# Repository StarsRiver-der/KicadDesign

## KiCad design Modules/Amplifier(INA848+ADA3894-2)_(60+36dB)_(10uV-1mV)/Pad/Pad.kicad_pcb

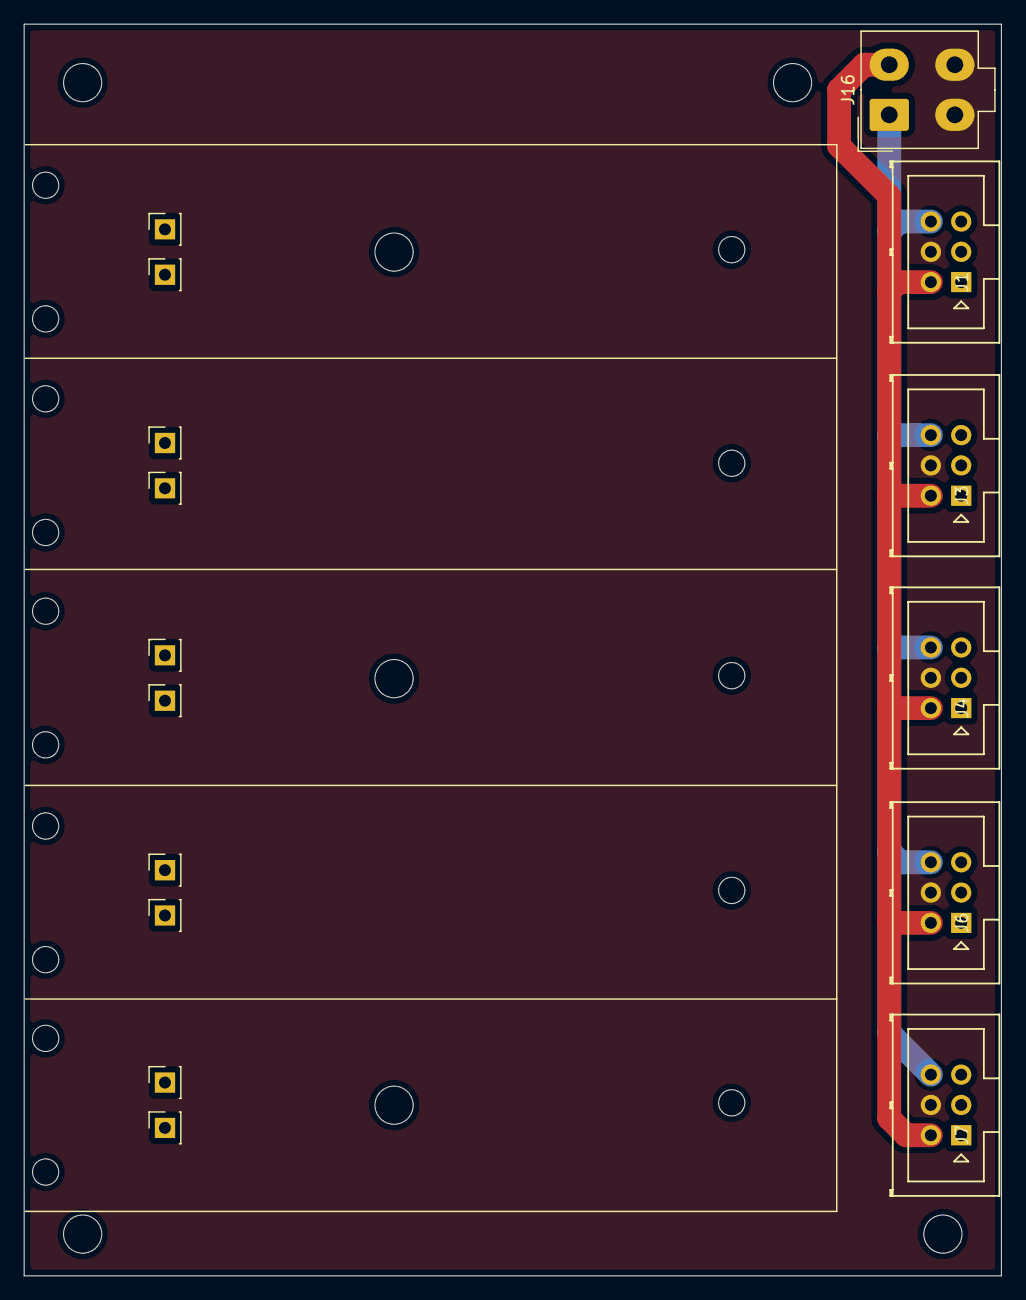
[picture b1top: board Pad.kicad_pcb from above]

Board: 4 copper layers, 81.9 x 104.9 mm, 38 parts (0 on the bottom side), 3 nets.

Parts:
H1, H2, H3, H4, H5, H6, H7, H8, H9, H10, H11, H12, H13, H14, H15: MountingHole; MountingHole_2.2mm_M2
H16, H17, H18, H19, H20, H22, H23: MountingHole; MountingHole_3.2mm_M3
J1, J3, J4, J6, J7: Conn_01x04; Multicomp_MC9A12-1034_2x03_P2.54mm_Vertical
J2, J5, J8, J9, J10, J11, J12, J13, J14, J15: Conn_01x01_Female; PinSocket_1x01_P2.54mm_Vertical
J16: Conn_01x04_Female; Molex_Mini-Fit_Jr_5566-04A_2x02_P4.20mm_Vertical

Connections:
+18V: J1.6, J3.6, J4.6, J6.6, J7.6, J16.1
-18V: J1.2, J3.2, J4.2, J6.2, J7.2, J16.2
GND: J1.4, J3.4, J4.4, J6.4, J7.4, J16.3, J16.4

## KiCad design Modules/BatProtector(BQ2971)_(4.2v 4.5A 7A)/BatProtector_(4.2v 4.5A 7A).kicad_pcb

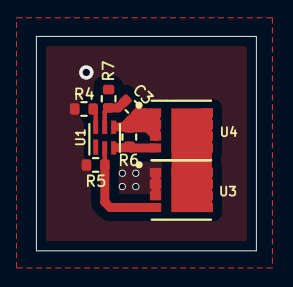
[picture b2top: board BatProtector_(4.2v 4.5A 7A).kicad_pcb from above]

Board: 2 copper layers, 12.2 x 11.9 mm, 8 parts (0 on the bottom side), 7 nets.

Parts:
C3: 0.1uF; C_0402_1005Metric
R4: 2.2k; R_0402_1005Metric
R5, R6: 5.1M; R_0402_1005Metric
R7: 330R; R_0402_1005Metric
U1: BQ2970; WSON-6_1.5x1.5mm_P0.5mm
U3, U4: CSD16406Q3

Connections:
BAT-: C3.2, R6.2, U1.4, U4.1, U4.2, U4.3
unnamed: C3.1, R7.2, U1.5
unnamed: R4.1, U1.6
unnamed: R5.1, U1.2, U3.4
unnamed: R6.1, U1.3, U4.4
unnamed: U3.5, U3.6, U3.7, U3.8, U4.5, U4.6, U4.7, U4.8
VDD: R4.2, R5.2, U3.1, U3.2, U3.3

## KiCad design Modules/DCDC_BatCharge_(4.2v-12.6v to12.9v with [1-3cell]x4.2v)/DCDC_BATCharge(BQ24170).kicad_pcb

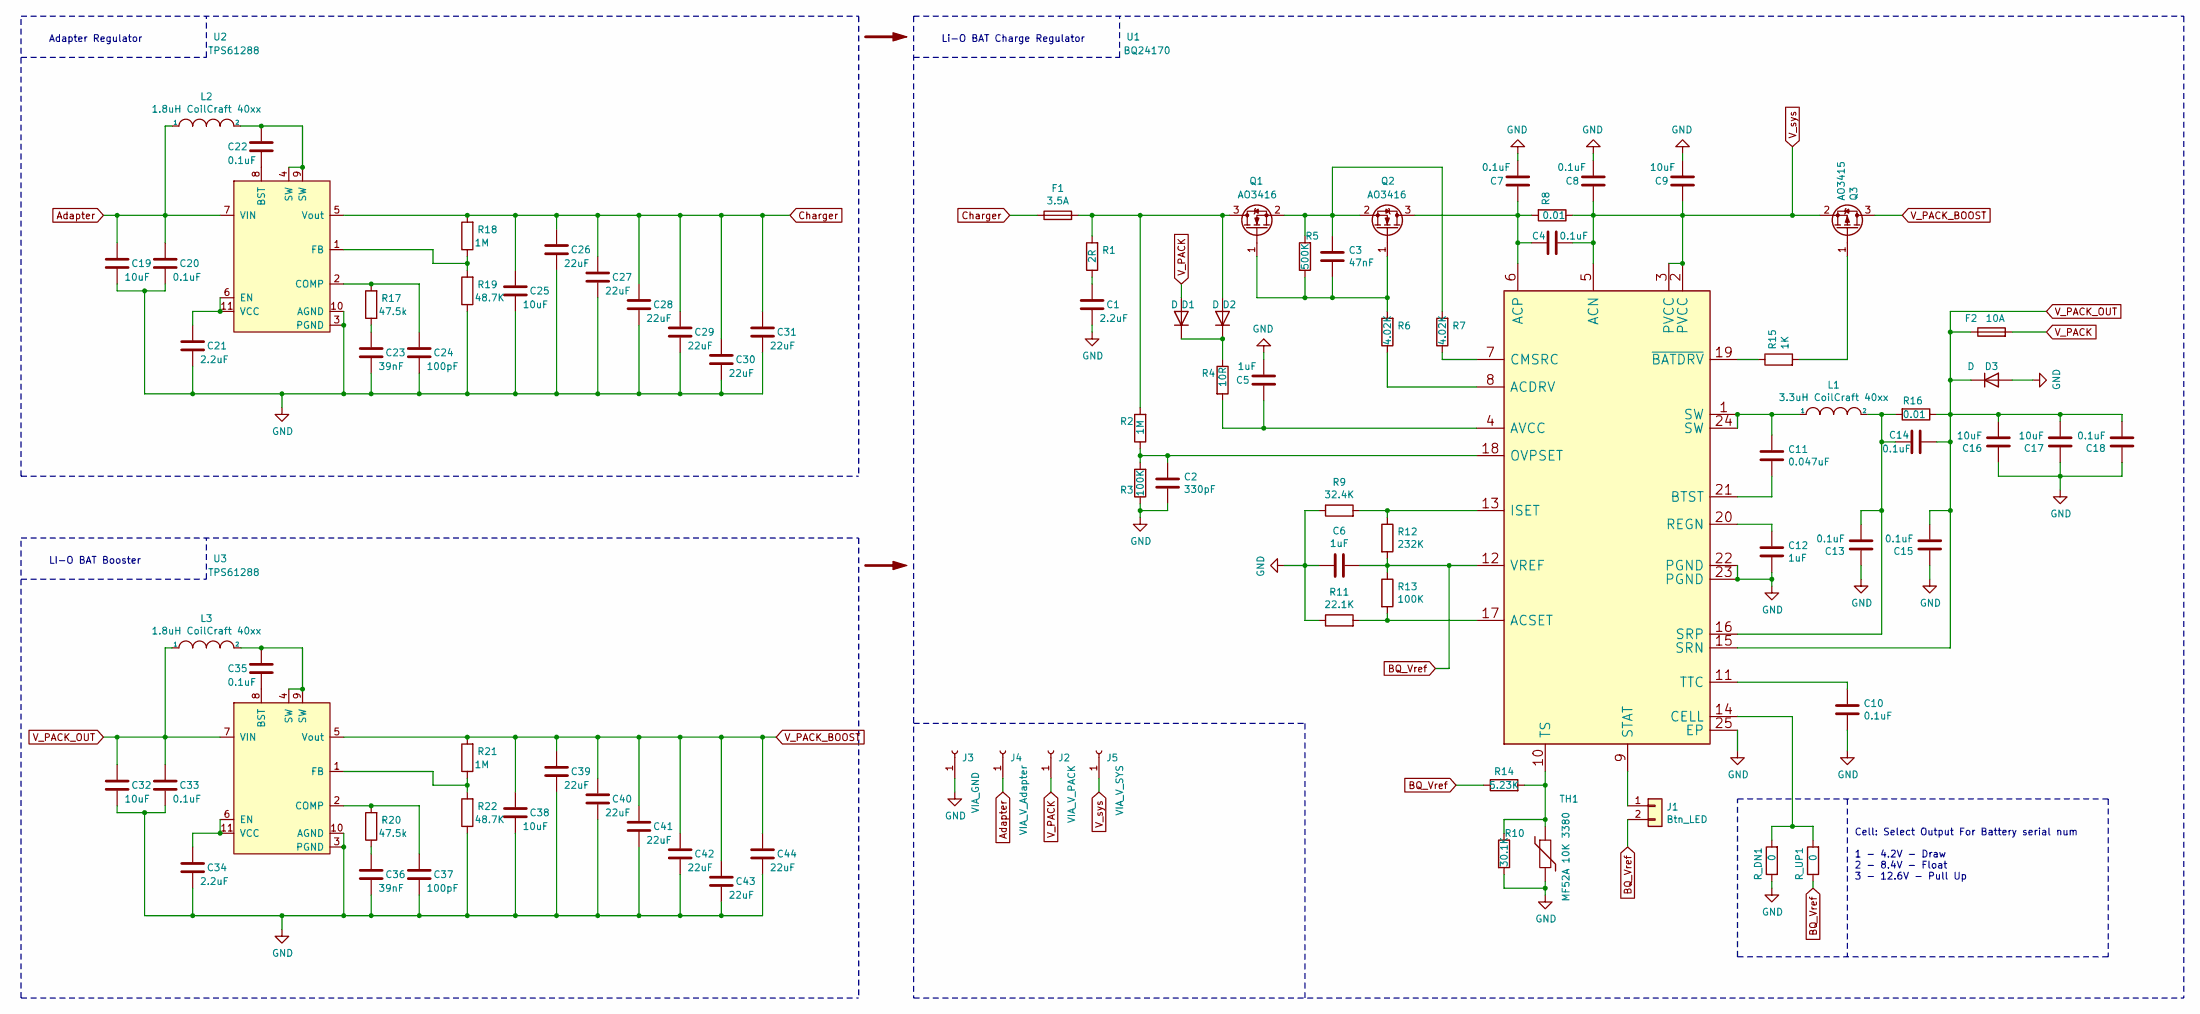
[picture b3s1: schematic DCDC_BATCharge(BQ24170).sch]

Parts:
C1, C21, C34: 2.2uF; C_0402_1005Metric
C2: 330pF; R_0402_1005Metric
C3: 47nF; C_0402_1005Metric
C4, C7, C8, C13, C14, C15, C20, C22, C33, C35: 0.1uF; C_0402_1005Metric
C5, C6, C12: 1uF; C_0603_1608Metric
C9, C16, C17: 10uF; C_0805_2012Metric
C10, C18: 0.1uF; C_0603_1608Metric
C11: 0.047uF; C_0402_1005Metric
C19, C25, C32, C38: 10uF; C_0603_1608Metric
C23, C36: 39nF; C_0402_1005Metric
C24, C37: 100pF; C_0402_1005Metric
C26, C27, C28, C29, C30, C31, C39, C40, C41, C42, C43, C44: 22uF; C_0805_2012Metric
D1, D2, D3: D; D_0603_1608Metric
F1: 3.5A; Fuse_0603_1608Metric
F2: 10A; Fuse_0603_1608Metric
J1: Btn_LED; PinHeader_1x02_P1.00mm_Vertical
J2: VIA_V_PACK; MountingHole_2.2mm_M2_Pad_Via
J3: VIA_GND; MountingHole_2.2mm_M2_Pad_Via
J4: VIA_V_Adapter; MountingHole_2.2mm_M2_Pad_Via
J5: VIA_V_SYS; MountingHole_2.2mm_M2_Pad_Via
L1: 3.3uH CoilCraft 40xx; L_Coilcraft_XxL4020
L2, L3: 1.8uH CoilCraft 40xx; L_Coilcraft_XxL4020
Q1, Q2: AO3416; SOT-23
Q3: AO3415; SOT-23
R1: 2R; R_0402_1005Metric
R2, R18, R21: 1M; R_0402_1005Metric
R3, R13: 100K; R_0402_1005Metric
R4: 10R; R_0402_1005Metric
R5: 500K; R_0402_1005Metric
R6, R7: 4.02K; R_0402_1005Metric
R8, R16: 0.01; R_0805_2012Metric
R9: 32.4K; R_0402_1005Metric
R10: 30.1K; R_0402_1005Metric
R11: 22.1K; R_0402_1005Metric
R12: 232K; R_0402_1005Metric
R14: 5.23K; R_0402_1005Metric
R15: 1K; R_0402_1005Metric
R17, R20: 47.5k; R_0402_1005Metric
R19, R22: 48.7K; R_0402_1005Metric
R_DN1: 0; R_0402_1005Metric
R_UP1: 0; R_0402_1005Metric
TH1: MF52A 10K 3380; R_Axial_DIN0204_L3.6mm_D1.6mm_P1.90mm_Vertical
U1: BQ24170; BQ24170RGYT
U2, U3: TPS61288

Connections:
Adapter: C19.2, C20.2, J4.1, L2.1, U2.7 (VIN)
BQ_Vref: C6.1, J1.2, R12.2, R13.1, R14.1, R_UP1.1, U1.12 (VREF)
Charger: C25.2, C26.2, C27.2, C28.2, C29.2, C30.2, C31.2, F1.1, R18.2, U2.5 (Vout)
GND: C1.1, C2.1, C5.1, C6.2, C7.1, C8.1, C9.1, C10.2, C12.2, C13.1, C15.1, C16.1, C17.1, C18.1, C19.1, C20.1, C21.1, C23.1, C24.1, C25.1, C26.1, C27.1, C28.1, C29.1, C30.1, C31.1, C32.1, C33.1, C34.1, C36.1, C37.1, C38.1, C39.1, C40.1, C41.1, C42.1, C43.1, C44.1, D3.2 (A), J3.1, R3.1, R9.1, R10.2, R11.1, R19.1, R22.1, R_DN1.1, TH1.2, U1.22 (PGND), U1.23 (PGND), U1.25 (EP), U2.3 (PGND), U2.10 (AGND), U3.3 (PGND), U3.10 (AGND)
unnamed: C1.2, R1.1
unnamed: C2.2, R2.1, R3.2, U1.18 (OVPSET)
unnamed: C3.1, Q1.1 (G), Q2.1 (G), R5.1, R6.2
unnamed: C3.2, Q1.2 (S), Q2.2 (S), R5.2, R7.2
unnamed: C4.1, C7.2, Q2.3 (D), R8.2, U1.6 (ACP)
unnamed: C5.2, R4.2, U1.4 (AVCC)
unnamed: C10.1, U1.11 (TTC)
unnamed: C11.1, L1.1, U1.1 (SW), U1.24 (SW)
unnamed: C11.2, U1.21 (BTST)
unnamed: C12.1, U1.20 (REGN)
unnamed: C13.2, C14.2, L1.2, R16.2, U1.16 (SRP)
unnamed: C21.2, U2.6 (EN), U2.11 (VCC)
unnamed: C22.1, U2.8 (BST)
unnamed: C22.2, L2.2, U2.4 (SW), U2.9 (SW)
unnamed: C23.2, R17.1
unnamed: C24.2, R17.2, U2.2 (COMP)
unnamed: C34.2, U3.6 (EN), U3.11 (VCC)
unnamed: C35.1, U3.8 (BST)
unnamed: C35.2, L3.2, U3.4 (SW), U3.9 (SW)
unnamed: C36.2, R20.1
unnamed: C37.2, R20.2, U3.2 (COMP)
unnamed: D1.1 (K), D2.1 (K), R4.1
unnamed: D2.2 (A), F1.2, Q1.3 (D), R1.2, R2.2
unnamed: J1.1, U1.9 (STAT)
unnamed: Q3.1 (G), R15.2
unnamed: R6.1, U1.8 (ACDRV)
unnamed: R7.1, U1.7 (CMSRC)
unnamed: R10.1, R14.2, TH1.1, U1.10 (TS)
unnamed: R11.2, R13.2, U1.17 (ACSET)
unnamed: R9.2, R12.1, U1.13 (ISET)
unnamed: R15.1, U1.19 (~BATDRV)
unnamed: R18.1, R19.2, U2.1 (FB)
unnamed: R21.1, R22.2, U3.1 (FB)
unnamed: R_DN1.2, R_UP1.2, U1.14 (CELL)
V_PACK: D1.2 (A), F2.2, J2.1
V_PACK_BOOST: C38.2, C39.2, C40.2, C41.2, C42.2, C43.2, C44.2, Q3.3 (D), R21.2, U3.5 (Vout)
V_PACK_OUT: C14.1, C15.2, C16.2, C17.2, C18.2, C32.2, C33.2, D3.1 (K), F2.1, L3.1, R16.1, U1.15 (SRN), U3.7 (VIN)
V_sys: C4.2, C8.2, C9.2, J5.1, Q3.2 (S), R8.1, U1.2 (PVCC), U1.3 (PVCC), U1.5 (ACN)

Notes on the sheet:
Li-O BAT Charge Regulator
Adapter Regulator
LI-O BAT Booster
Cell: Select Output For Battery serial num 1 - 4.2V - Draw 2 - 8.4V - Float 3 - 12.6V - Pull Up

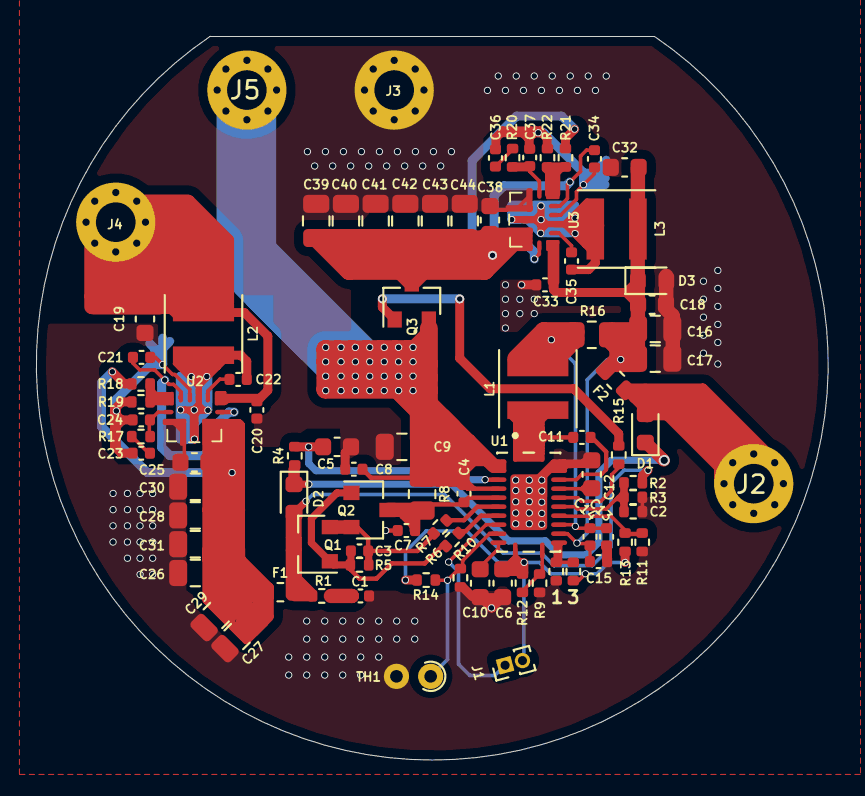
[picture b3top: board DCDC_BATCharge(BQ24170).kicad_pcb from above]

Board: 2 copper layers, 44.0 x 40.2 mm, 88 parts (0 on the bottom side), 42 nets.

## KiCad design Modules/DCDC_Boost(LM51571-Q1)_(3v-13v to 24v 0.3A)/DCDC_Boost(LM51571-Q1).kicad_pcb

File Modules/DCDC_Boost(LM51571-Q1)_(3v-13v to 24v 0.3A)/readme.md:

# 3V-13V 1-3串锂电池输入的 DCDC 升压电路
* 工作温度：0-85℃
* 最高0.8A 20W输出

# 原理
见说明手册

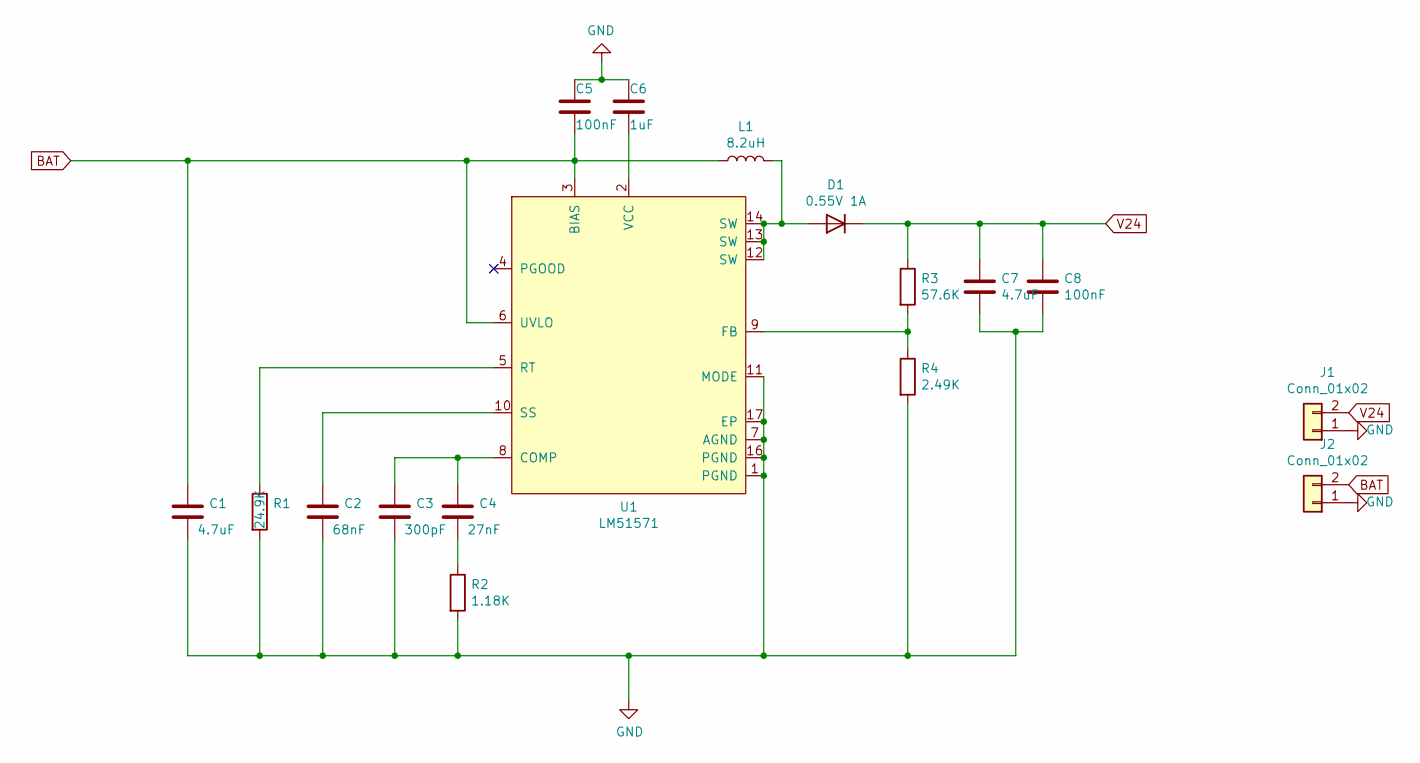
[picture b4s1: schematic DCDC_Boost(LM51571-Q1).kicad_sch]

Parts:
C1, C7: 4.7uF; C_0603_1608Metric
C2: 68nF; C_0402_1005Metric
C3: 300pF; C_0402_1005Metric
C4: 27nF; C_0402_1005Metric
C5, C8: 100nF; C_0402_1005Metric
C6: 1uF; C_0603_1608Metric
D1: 0.55V 1A; D_0603_1608Metric
J1, J2: Conn_01x02; PinHeader_1x02_P2.54mm_Vertical
L1: 8.2uH; L_Coilcraft_XxL4020
R1: 24.9K; R_0402_1005Metric
R2: 1.18K; R_0402_1005Metric
R3: 57.6K; R_0402_1005Metric
R4: 2.49K; R_0402_1005Metric
U1: LM51571; WQFN-16-1EP_3x3mm_P0.5mm_EP1.6x1.6mm_ThermalVias

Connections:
BAT: C1.1, C5.2, J2.2, L1.1, U1.3 (BIAS), U1.6 (UVLO)
GND: C1.2, C2.2, C3.2, C5.1, C6.1, C7.2, C8.2, J1.1, J2.1, R1.2, R2.2, R4.2, U1.1 (PGND), U1.7 (AGND), U1.11 (MODE), U1.16 (PGND), U1.17 (EP)
unnamed: C2.1, U1.10 (SS)
unnamed: C3.1, C4.1, U1.8 (COMP)
unnamed: C4.2, R2.1
unnamed: C6.2, U1.2 (VCC)
unnamed: D1.2 (A), L1.2, U1.12 (SW), U1.13 (SW), U1.14 (SW)
unnamed: R1.1, U1.5 (RT)
unnamed: R3.2, R4.1, U1.9 (FB)
V24: C7.1, C8.1, D1.1 (K), J1.2, R3.1

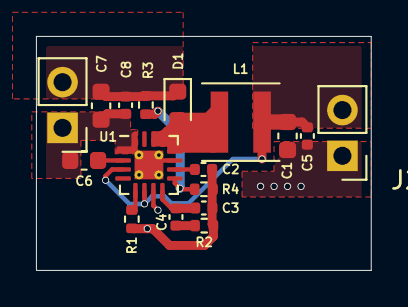
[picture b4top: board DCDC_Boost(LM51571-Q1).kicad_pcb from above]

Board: 2 copper layers, 18.6 x 13.0 mm, 17 parts (0 on the bottom side), 10 nets.

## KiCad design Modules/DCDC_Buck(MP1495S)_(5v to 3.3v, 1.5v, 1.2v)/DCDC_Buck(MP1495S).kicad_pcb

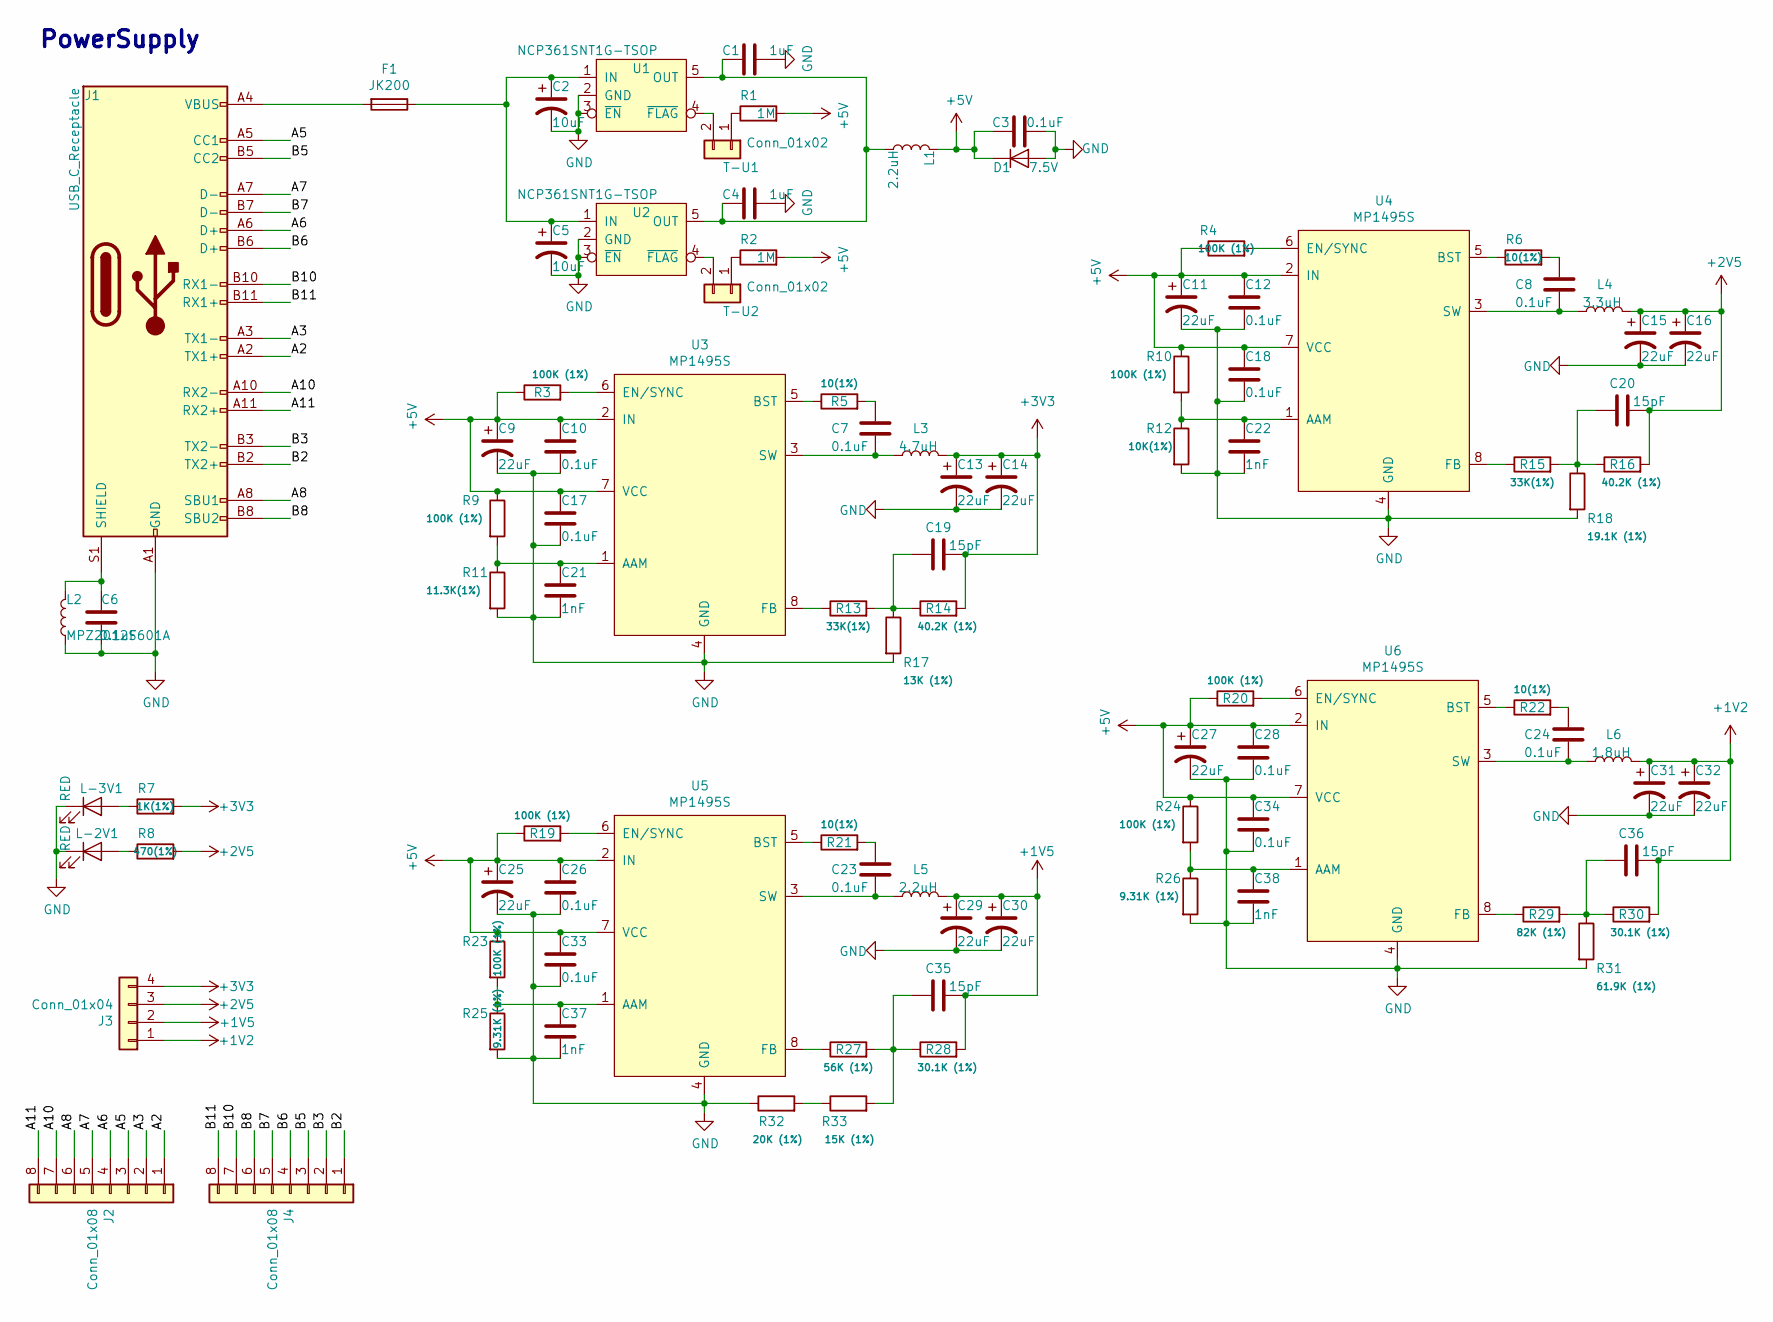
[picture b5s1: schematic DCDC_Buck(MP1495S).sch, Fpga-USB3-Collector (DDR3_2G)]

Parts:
C1, C4: 1uF; C_0603_1608Metric_Pad1.05x0.95mm_HandSolder
C2, C5: 10uF; C_0805_2012Metric_Pad1.15x1.40mm_HandSolder
C3, C6, C7, C8, C10, C12, C17, C18, C23, C24, C26, C28, C33, C34: 0.1uF; C_0603_1608Metric_Pad1.05x0.95mm_HandSolder
C9, C11, C13, C14, C15, C16, C25, C27, C29, C30, C31, C32: 22uF; C_0805_2012Metric_Pad1.15x1.40mm_HandSolder
C19, C20, C35, C36: 15pF; C_0603_1608Metric_Pad1.05x0.95mm_HandSolder
C21, C22, C37, C38: 1nF; C_0603_1608Metric_Pad1.05x0.95mm_HandSolder
D1: 7.5V; D_1206_3216Metric
F1: JK200; Fuse_2816_7142Metric_Pad3.20x4.45mm_HandSolder
J1: USB_C_Receptacle; USB_C_24pin_FtBp
J2, J4: Conn_01x08; PinHeader_1x08_P2.00mm_Vertical
J3: Conn_01x04; PinSocket_1x04_P2.54mm_Vertical
L1, L5: 2.2uH; L_Taiyo-Yuden_NR-60xx
L2: MPZ2012S601A; L_0805_2012Metric_Pad1.15x1.40mm_HandSolder
L3: 4.7uH; L_Taiyo-Yuden_NR-60xx
L4: 3.3uH; L_Taiyo-Yuden_NR-60xx
L6: 1.8uH; L_Taiyo-Yuden_NR-60xx
L-2V1, L-3V1: RED; LED_0603_1608Metric_Pad1.05x0.95mm_HandSolder
R1, R2: 1M; R_0603_1608Metric_Pad1.05x0.95mm_HandSolder
R3, R4, R9, R10, R19, R20, R23, R24: 100K (1%); R_0603_1608Metric_Pad1.05x0.95mm_HandSolder
R5, R6, R21, R22: 10(1%); R_0603_1608Metric_Pad1.05x0.95mm_HandSolder
R7: 1K(1%); R_0603_1608Metric_Pad1.05x0.95mm_HandSolder
R8: 470(1%); R_0603_1608Metric_Pad1.05x0.95mm_HandSolder
R11: 11.3K(1%); R_0603_1608Metric_Pad1.05x0.95mm_HandSolder
R12: 10K(1%); R_0603_1608Metric_Pad1.05x0.95mm_HandSolder
R13, R15: 33K(1%); R_0603_1608Metric_Pad1.05x0.95mm_HandSolder
R14, R16: 40.2K (1%); R_0603_1608Metric_Pad1.05x0.95mm_HandSolder
R17: 13K (1%); R_0603_1608Metric_Pad1.05x0.95mm_HandSolder
R18: 19.1K (1%); R_0603_1608Metric_Pad1.05x0.95mm_HandSolder
R25, R26: 9.31K (1%); R_0603_1608Metric_Pad1.05x0.95mm_HandSolder
R27: 56K (1%); R_0603_1608Metric_Pad1.05x0.95mm_HandSolder
R28, R30: 30.1K (1%); R_0603_1608Metric_Pad1.05x0.95mm_HandSolder
R29: 82K (1%); R_0603_1608Metric_Pad1.05x0.95mm_HandSolder
R31: 61.9K (1%); R_0603_1608Metric_Pad1.05x0.95mm_HandSolder
R32: 20K (1%); R_0603_1608Metric_Pad1.05x0.95mm_HandSolder
R33: 15K (1%); R_0603_1608Metric_Pad1.05x0.95mm_HandSolder
T-U1, T-U2: Conn_01x02; Pad_1x02_P2.54mm
U1, U2: NCP361SNT1G-TSOP; TSOP-5_1.65x3.05mm_P0.95mm
U3, U4, U5, U6: MP1495S; SOT65P280X100-8N

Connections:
+1V2: C31.1, C32.1, C36.2, J3.1, L6.2, R30.2
+1V5: C29.1, C30.1, C35.2, J3.2, L5.2, R28.2
+2V5: C15.1, C16.1, C20.2, J3.3, L4.2, R8.2, R16.2
+3V3: C13.1, C14.1, C19.2, J3.4, L3.2, R7.2, R14.2
+5V: C3.1, C9.1, C10.1, C11.1, C12.1, C17.1, C18.1, C25.1, C26.1, C27.1, C28.1, C33.1, C34.1, D1.1 (K), L1.1, R1.2, R2.2, R3.1, R4.1, R9.1, R10.1, R19.1, R20.1, R23.1, R24.1, U3.2 (IN), U3.7 (VCC), U4.2 (IN), U4.7 (VCC), U5.2 (IN), U5.7 (VCC), U6.2 (IN), U6.7 (VCC)
/A2: J1.A2 (TX1+), J2.1
/A3: J1.A3 (TX1-), J2.2
/A5: J1.A5 (CC1), J2.3
/A6: J1.A6 (D+), J2.4
/A7: J1.A7 (D-), J2.5
/A8: J1.A8 (SBU1), J2.6
/A10: J1.A10 (RX2-), J2.7
/A11: J1.A11 (RX2+), J2.8
/B2: J1.B2 (TX2+), J4.1
/B3: J1.B3 (TX2-), J4.2
/B5: J1.B5 (CC2), J4.3
/B6: J1.B6 (D+), J4.4
/B7: J1.B7 (D-), J4.5
/B8: J1.B8 (SBU2), J4.6
/B10: J1.B10 (RX1-), J4.7
/B11: J1.B11 (RX1+), J4.8
GND: C1.2, C2.2, C3.2, C4.2, C5.2, C6.2, C9.2, C10.2, C11.2, C12.2, C13.2, C14.2, C15.2, C16.2, C17.2, C18.2, C21.2, C22.2, C25.2, C26.2, C27.2, C28.2, C29.2, C30.2, C31.2, C32.2, C33.2, C34.2, C37.2, C38.2, D1.2 (A), J1.A1 (GND), J1.A12 (GND), J1.B1 (GND), J1.B12 (GND), L2.2, L-2V1.1 (K), L-3V1.1 (K), R11.2, R12.2, R17.2, R18.2, R25.2, R26.2, R31.2, R32.1, U1.2 (GND), U1.3 (~EN), U2.2 (GND), U2.3 (~EN), U3.4 (GND), U4.4 (GND), U5.4 (GND), U6.4 (GND)
unnamed: C1.1, C4.1, L1.2, U1.5 (OUT), U2.5 (OUT)
unnamed: C2.1, C5.1, F1.1, U1.1 (IN), U2.1 (IN)
unnamed: C6.1, J1.S1 (SHIELD), L2.1
unnamed: C7.1, R5.2
unnamed: C7.2, L3.1, U3.3 (SW)
unnamed: C8.1, R6.2
unnamed: C8.2, L4.1, U4.3 (SW)
unnamed: C19.1, R13.2, R14.1, R17.1
unnamed: C20.1, R15.2, R16.1, R18.1
unnamed: C21.1, R9.2, R11.1, U3.1 (AAM)
unnamed: C22.1, R10.2, R12.1, U4.1 (AAM)
unnamed: C23.1, R21.2
unnamed: C23.2, L5.1, U5.3 (SW)
unnamed: C24.1, R22.2
unnamed: C24.2, L6.1, U6.3 (SW)
unnamed: C35.1, R27.2, R28.1, R33.2
unnamed: C36.1, R29.2, R30.1, R31.1
unnamed: C37.1, R23.2, R25.1, U5.1 (AAM)
unnamed: C38.1, R24.2, R26.1, U6.1 (AAM)
unnamed: F1.2, J1.A4 (VBUS), J1.A9 (VBUS), J1.B4 (VBUS), J1.B9 (VBUS)
unnamed: L-2V1.2 (A), R8.1
unnamed: L-3V1.2 (A), R7.1
unnamed: R1.1, T-U1.1
unnamed: R2.1, T-U2.1
unnamed: R3.2, U3.6 (EN/SYNC)
unnamed: R4.2, U4.6 (EN/SYNC)
unnamed: R5.1, U3.5 (BST)
unnamed: R6.1, U4.5 (BST)
unnamed: R13.1, U3.8 (FB)
unnamed: R15.1, U4.8 (FB)
unnamed: R19.2, U5.6 (EN/SYNC)
unnamed: R20.2, U6.6 (EN/SYNC)
unnamed: R21.1, U5.5 (BST)
unnamed: R22.1, U6.5 (BST)
unnamed: R27.1, U5.8 (FB)
unnamed: R29.1, U6.8 (FB)
unnamed: R32.2, R33.1
unnamed: T-U1.2, U1.4 (~FLAG)
unnamed: T-U2.2, U2.4 (~FLAG)

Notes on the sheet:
PowerSupply

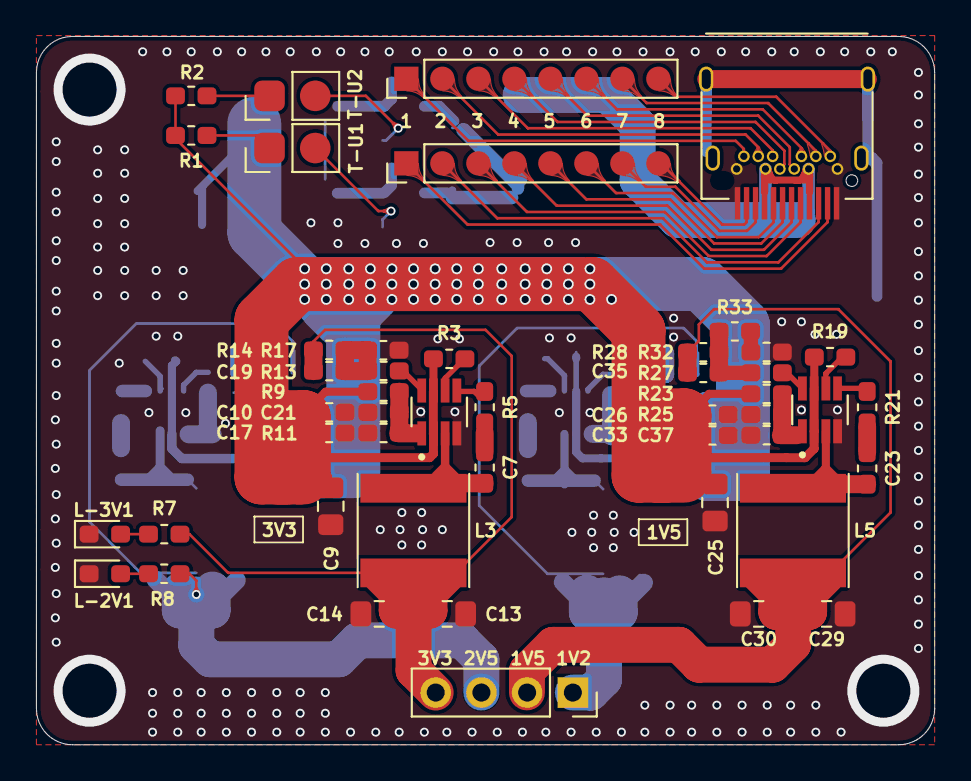
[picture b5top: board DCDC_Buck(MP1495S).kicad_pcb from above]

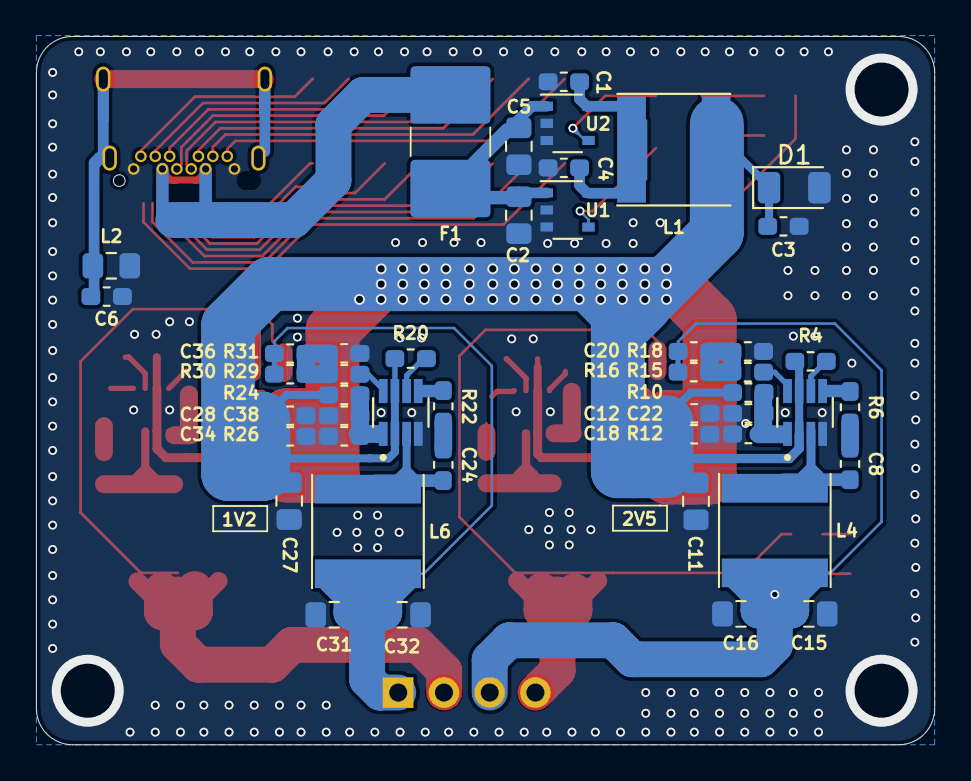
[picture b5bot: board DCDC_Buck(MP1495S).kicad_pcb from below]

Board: 2 copper layers, 49.9 x 39.4 mm, 93 parts (46 on the bottom side), 61 nets.

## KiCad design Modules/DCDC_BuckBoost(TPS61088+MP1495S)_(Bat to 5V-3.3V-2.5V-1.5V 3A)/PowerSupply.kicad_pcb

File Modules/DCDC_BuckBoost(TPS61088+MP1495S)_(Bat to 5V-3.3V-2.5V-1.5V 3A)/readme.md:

# 2.8V-4.2V 锂电池输入的 DCDC 单极性多轨电源
* 工作温度：0-85℃
* 5V、3.3V、2.5V、1.5V多轨输出
* 最高20W输出

# 原理
见说明手册

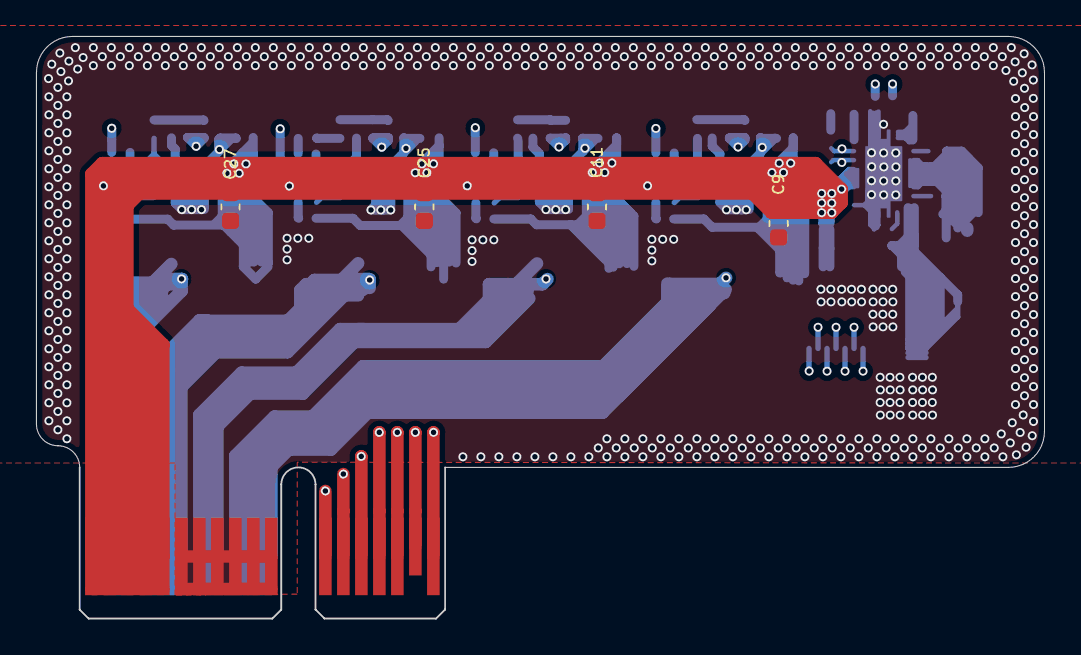
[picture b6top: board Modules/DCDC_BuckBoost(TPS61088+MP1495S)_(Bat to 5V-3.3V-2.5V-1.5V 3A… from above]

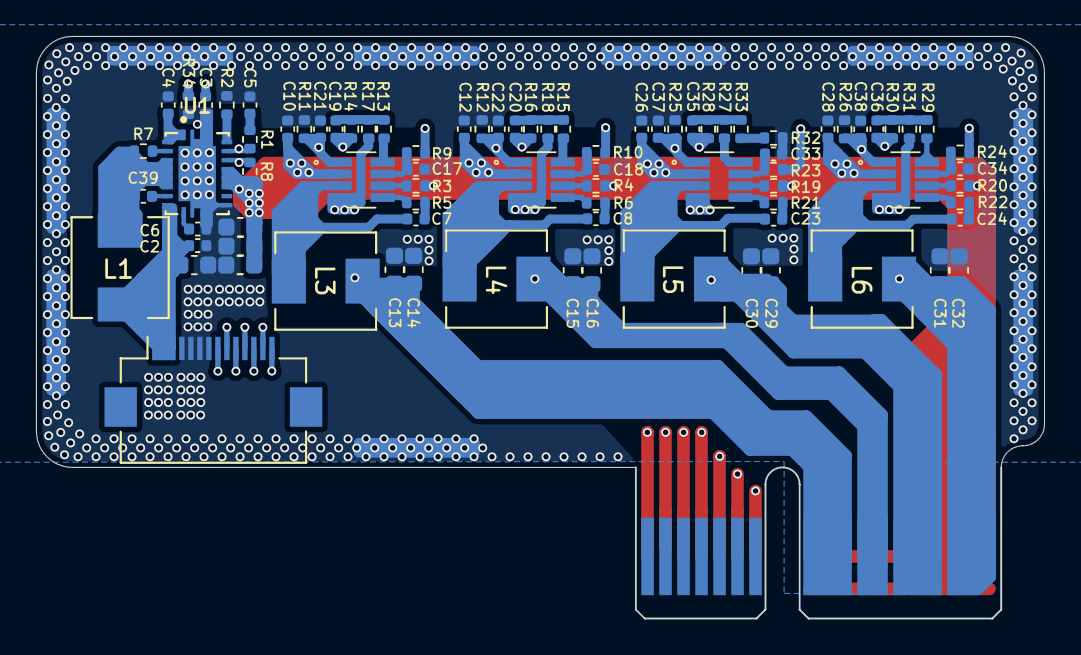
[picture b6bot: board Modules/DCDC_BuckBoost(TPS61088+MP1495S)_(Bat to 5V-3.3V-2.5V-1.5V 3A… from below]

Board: 4 copper layers, 56.0 x 32.3 mm, 97 parts (92 on the bottom side), 56 nets.

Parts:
1V2, 1V5, 2V5, 3V3: MP1495S; SOT65P280X100-8N
C1, C9, C11, C25, C27: 10uF; C_0603_1608Metric
C2, C7, C8, C10, C12, C17, C18, C23, C24, C26, C28, C33, C34, C39: 0.1uF; C_0402_1005Metric
C3: 47pF; C_0402_1005Metric
C4: 1uF; C_0402_1005Metric
C5, C21, C22, C37, C38: 1nF; C_0402_1005Metric
C6: 8.2nF; C_0402_1005Metric
C13, C14, C15, C16, C29, C30, C31, C32, C40, C41, C42: 22uF; C_0603_1608Metric
C19, C20, C35, C36: 15pF; C_0402_1005Metric
J1: Conn_01x14; Hirose_FH12-14S-0.5SH_1x14-1MP_P0.50mm_Horizontal
J2, J3, J4, J5, J6, J7, J8, J9, J10: Conn_01x01; pad-6-1.5
L1: 1uH; L_Sunlord_MWSA0518_5.4x5.2mm
L3: 4.7uH; L_Sunlord_MWSA0518_5.4x5.2mm
L4: 3.3uH; L_Sunlord_MWSA0518_5.4x5.2mm
L5: 2.2uH; L_Sunlord_MWSA0518_5.4x5.2mm
L6: 1.8uH; L_Sunlord_MWSA0518_5.4x5.2mm
PCI1: Conn_02x18_Row_Letter_First; BUS_PCIexpress_x1
R1: 23.7K; R_0402_1005Metric
R2: 113K; R_0402_1005Metric
R3, R4, R9, R10, R19, R20, R23, R24: 100K (1%); R_0402_1005Metric
R5, R6, R21, R22: 10(1%); R_0402_1005Metric
R7: 267K; R_0402_1005Metric
R8: 220K; R_0402_1005Metric
R11: 11.3K(1%); R_0402_1005Metric
R12: 10K(1%); R_0402_1005Metric
R13, R15: 33K(1%); R_0402_1005Metric
R14, R16: 40.2K (1%); R_0402_1005Metric
R17: 13K (1%); R_0402_1005Metric
R18: 19.1K (1%); R_0402_1005Metric
R25, R26: 9.31K (1%); R_0402_1005Metric
R27: 56K (1%); R_0402_1005Metric
R28, R30: 30.1K (1%); R_0402_1005Metric
R29: 82K (1%); R_0402_1005Metric
R31: 61.9K (1%); R_0402_1005Metric
R32: 20K (1%); R_0402_1005Metric
R33: 15K (1%); R_0402_1005Metric
R34: 69.8K; R_0402_1005Metric
U1: TPS61088RHLR; IC_TPS61088RHLR

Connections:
+1V2: C31.1, C32.1, C36.2, L6.2, PCI1.A1, PCI1.A2, PCI1.A3, R30.2
+1V5: C29.1, C30.1, C35.2, L5.2, PCI1.A4, PCI1.A5, PCI1.A6, R28.2
+2V5: C15.1, C16.1, C20.2, L4.2, PCI1.A7, PCI1.A8, R16.2
+3V3: C13.1, C14.1, C19.2, L3.2, PCI1.A9, PCI1.A10, PCI1.A11, R14.2
+5V: 1V2.2, 1V5.2, 2V5.2, 3V3.2, C9.1, C10.1, C11.1, C12.1, C25.1, C26.1, C27.1, C28.1, C40.1, C41.1, C42.1, PCI1.B1, PCI1.B2, PCI1.B3, PCI1.B4, PCI1.B5, R3.1, R4.1, R8.2, R19.1, R20.1, U1.14, U1.15, U1.16
BAT+: C1.1, C2.1, J1.1, J1.2, J1.3, L1.1, U1.9
BAT_CHG: J1.8, PCI1.B18
BAT_ISET: J1.10, PCI1.B16
BAT_PG: J1.9, PCI1.B17
GND: 1V2.4, 1V5.4, 2V5.4, 3V3.4, C1.2, C2.2, C3.2, C4.2, C5.2, C6.2, C9.2, C10.2, C11.2, C12.2, C13.2, C14.2, C15.2, C16.2, C17.2, C18.2, C21.2, C22.2, C25.2, C26.2, C27.2, C28.2, C29.2, C30.2, C31.2, C32.2, C33.2, C34.2, C37.2, C38.2, C40.2, C41.2, C42.2, J1.4, J1.5, J1.6, J1.7, J2.1, J3.1, J4.1, J5.1, J6.1, J7.1, J8.1, J9.1, J10.1, PCI1.B6, PCI1.B7, PCI1.B8, PCI1.B9, PCI1.B10, PCI1.B11, R2.2, R11.2, R12.2, R17.2, R18.2, R25.2, R26.2, R31.2, R32.1, R34.1, U1.11, U1.12, U1.20, U1.21
unnamed: 1V2.1, C38.1, R24.2, R26.1
unnamed: 1V2.3, C24.2, L6.1
unnamed: 1V2.5, R22.1
unnamed: 1V2.6, R20.2
unnamed: 1V2.7, C34.1, R24.1
unnamed: 1V2.8, R29.1
unnamed: 1V5.1, C37.1, R23.2, R25.1
unnamed: 1V5.3, C23.2, L5.1
unnamed: 1V5.5, R21.1
unnamed: 1V5.6, R19.2
unnamed: 1V5.7, C33.1, R23.1
unnamed: 1V5.8, R27.1
unnamed: 2V5.1, C22.1, R10.2, R12.1
unnamed: 2V5.3, C8.2, L4.1
unnamed: 2V5.5, R6.1
unnamed: 2V5.6, R4.2
unnamed: 2V5.7, C18.1, R10.1
unnamed: 2V5.8, R15.1
unnamed: 3V3.1, C21.1, R9.2, R11.1
unnamed: 3V3.3, C7.2, L3.1
unnamed: 3V3.5, R5.1
unnamed: 3V3.6, R3.2
unnamed: 3V3.7, C17.1, R9.1
unnamed: 3V3.8, R13.1
unnamed: C3.1, R1.1, U1.18
unnamed: C4.1, U1.1, U1.2
unnamed: C5.1, R1.2
unnamed: C6.1, U1.10
unnamed: C7.1, R5.2
unnamed: C8.1, R6.2
unnamed: C19.1, R13.2, R14.1, R17.1
unnamed: C20.1, R15.2, R16.1, R18.1
unnamed: C23.1, R21.2
unnamed: C24.1, R22.2
unnamed: C35.1, R27.2, R28.1, R33.2
unnamed: C36.1, R29.2, R30.1, R31.1
unnamed: C39.1, U1.8
unnamed: C39.2, L1.2, R7.2, U1.4, U1.5, U1.6, U1.7
unnamed: R2.1, U1.19
unnamed: R7.1, U1.3
unnamed: R32.2, R33.1
unnamed: R8.1, R34.2, U1.17
REG_CHG: J1.12, PCI1.B14
REG_EN1: J1.13, PCI1.B13
REG_EN2: J1.14, PCI1.B12
REG_POWER: J1.11, PCI1.B15
